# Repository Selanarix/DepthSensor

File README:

DepthSensor Project
====================

Copyright (c) 2014 Jonathan Schubert and Maximilian Hempe

About the repo
--------------
This repository contains code to realise a depth sensor by using an arduino uno and a differential pressure sensor. By transfering the pressure to water depth (1cm=1hPa) the arduino messures the water depth and gives it to a server, which produces a graph on a webpage. We do not give any garantee, but in tests it worked very well.

Purpose
--------
The Project should give a cost efficient method to messure the amount of water in an underground cistern. Additionally it can give statistics about water usage peak times.

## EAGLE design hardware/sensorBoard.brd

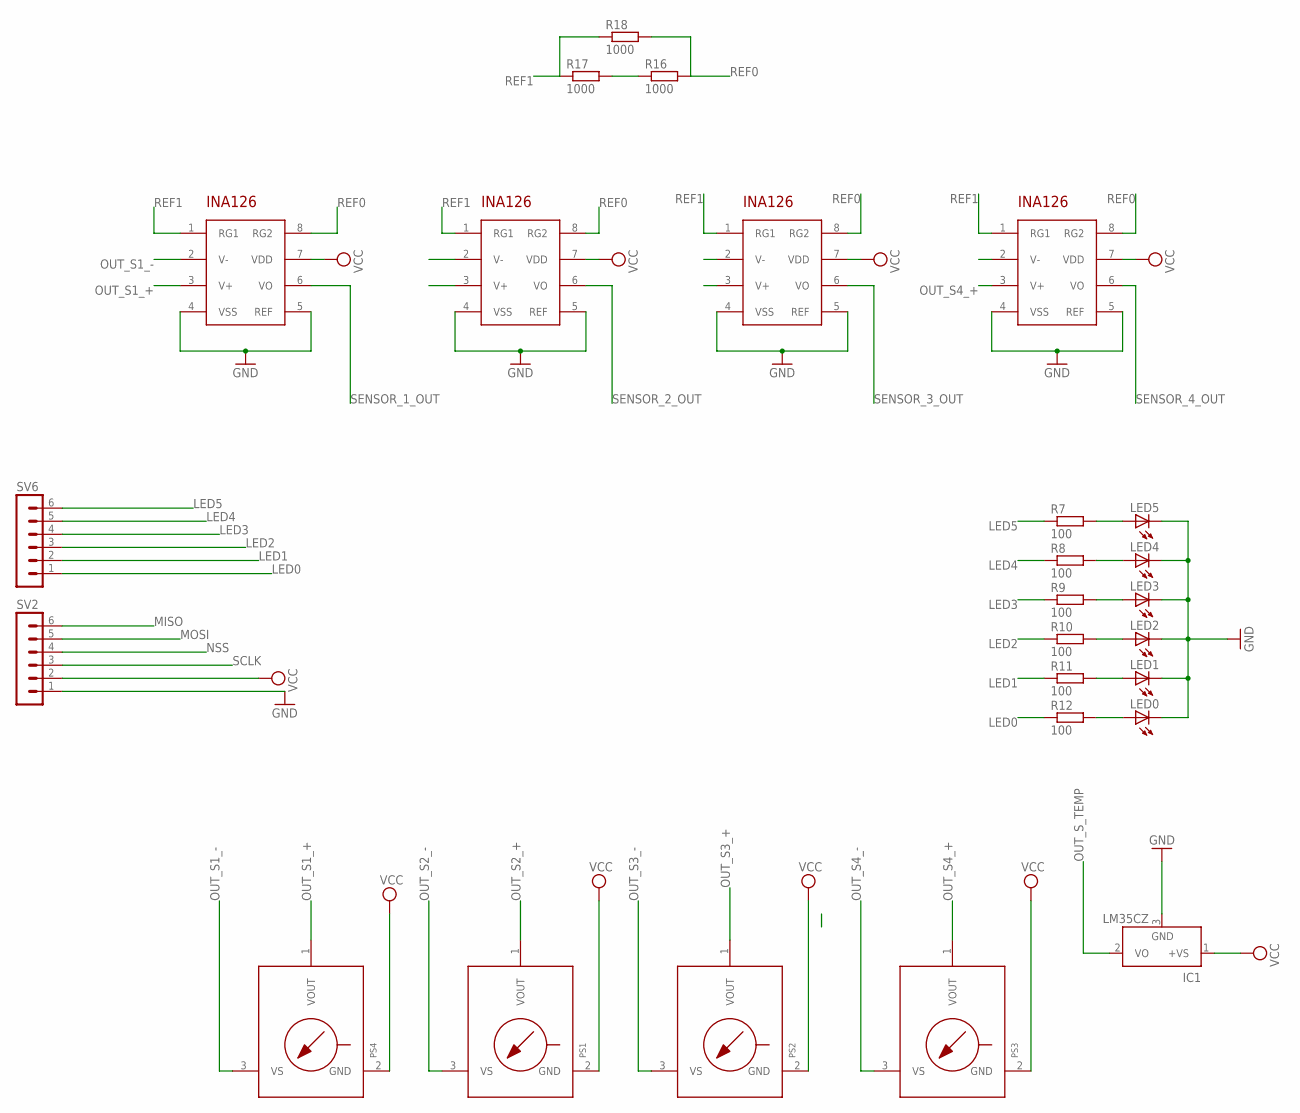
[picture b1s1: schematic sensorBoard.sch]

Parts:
IC1: LM35CZ; TO92
LED0, LED1, LED2, LED3, LED4, LED5: LED3MM
PS1, PS2, PS3, PS4: MPX-867B-H; 867B-H
R7, R8, R9, R10, R11, R12: 100; 0207/10
R16, R17, R18: 1000; 0207/10
SV2, SV6: MA06-1
U$1, U$2, U$3, U$4: INA126; SO-08

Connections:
GND: IC1.3 (GND), LED0.K (C), LED1.K (C), LED2.K (C), LED3.K (C), LED4.K (C), LED5.K (C), SV2.1, U$1.4 (VSS), U$1.5 (REF), U$2.4 (VSS), U$2.5 (REF), U$3.4 (VSS), U$3.5 (REF), U$4.4 (VSS), U$4.5 (REF)
LED0: R12.1, SV6.1
LED1: R11.1, SV6.2
LED2: R10.1, SV6.3
LED3: R9.1, SV6.4
LED4: R8.1, SV6.5
LED5: R7.1, SV6.6
MISO: SV2.6
MOSI: SV2.5
unnamed: LED5.A, R7.2
unnamed: R16.1, R17.2
unnamed: LED4.A, R8.2
unnamed: LED3.A, R9.2
unnamed: LED2.A, R10.2
unnamed: LED1.A, R11.2
unnamed: LED0.A, R12.2
NSS: SV2.4
OUT_S1_+: PS4.1 (VOUT)
OUT_S1_-: PS4.3 (VS)
OUT_S2_+: PS1.1 (VOUT)
OUT_S2_-: PS1.3 (VS)
OUT_S3_+: PS2.1 (VOUT)
OUT_S3_-: PS2.3 (VS)
OUT_S4_+: PS3.1 (VOUT)
OUT_S4_-: PS3.3 (VS)
OUT_S_TEMP: IC1.2 (VO)
REF0: R16.2, R18.2
REF1: R17.1, R18.1
SCLK: SV2.3
SENSOR_1_OUT: U$4.6 (VO)
SENSOR_2_OUT: U$1.6 (VO)
SENSOR_3_OUT: U$2.6 (VO)
SENSOR_4_OUT: U$3.6 (VO)
VCC: IC1.1 (+VS), PS1.2 (GND), PS2.2 (GND), PS3.2 (GND), PS4.2 (GND), SV2.2, U$1.7 (VDD), U$2.7 (VDD), U$3.7 (VDD), U$4.7 (VDD)

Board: 2 copper layers, 26 parts (0 on the bottom side), 17 nets, no tracks yet.

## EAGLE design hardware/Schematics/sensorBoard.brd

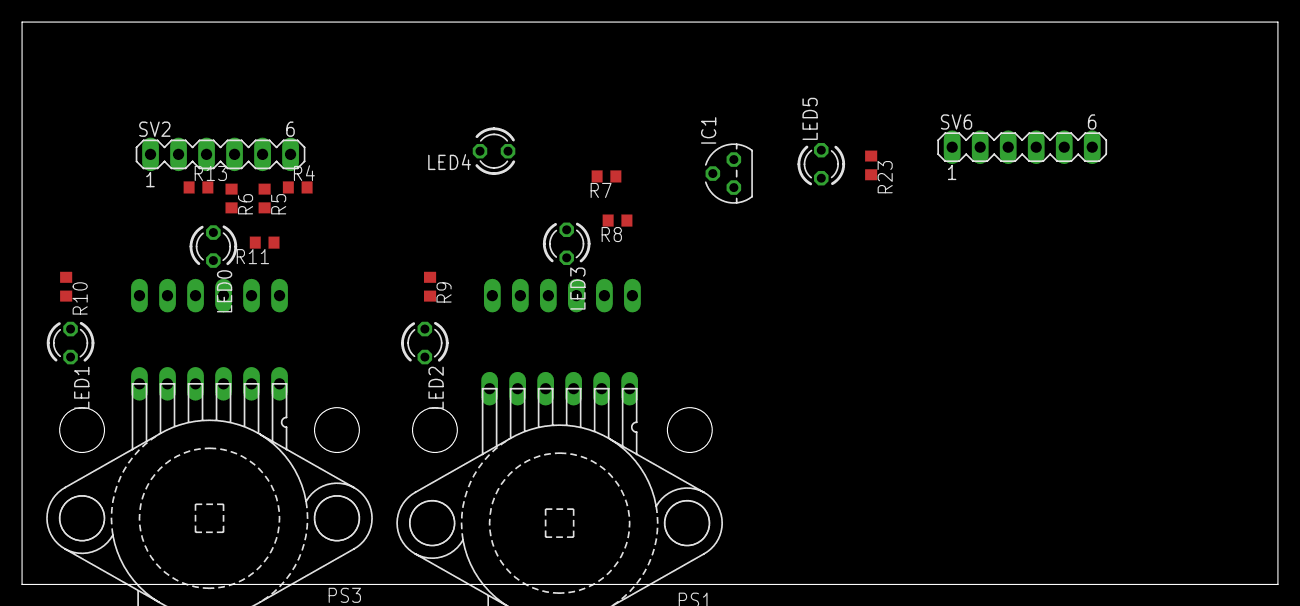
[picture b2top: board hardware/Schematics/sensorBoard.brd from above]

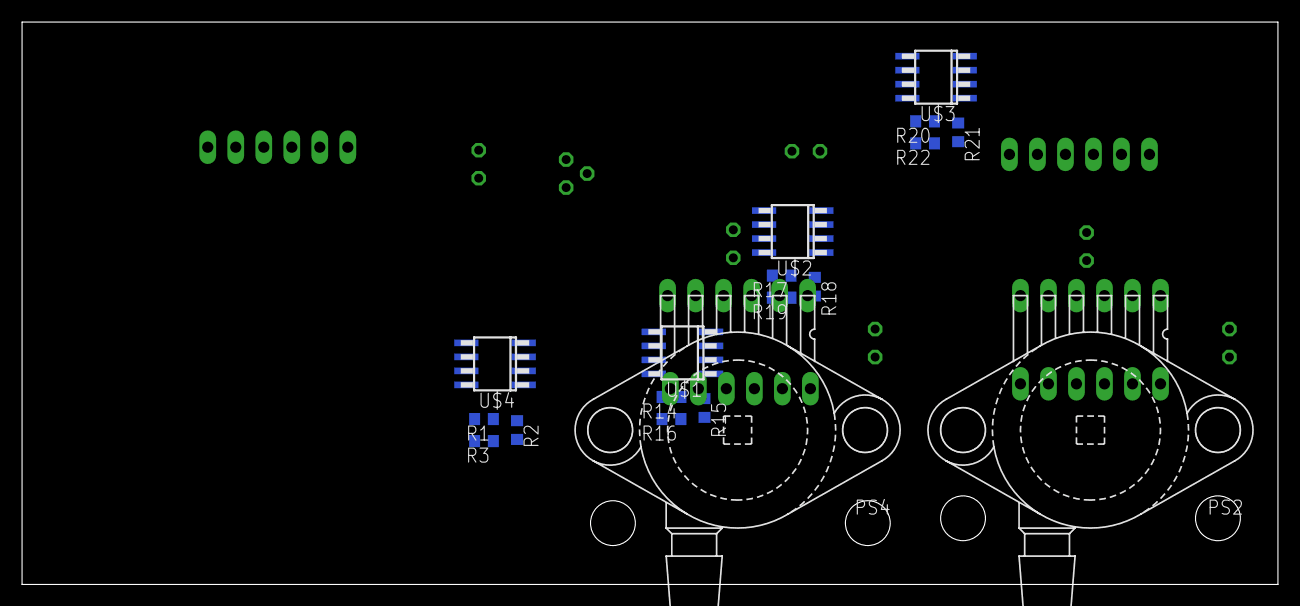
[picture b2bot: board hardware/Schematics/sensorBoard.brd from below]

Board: 2 copper layers, 113.9 x 51.0 mm, 39 parts (18 on the bottom side), 30 nets, no tracks yet.

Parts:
IC1: LM35CZ; TO92
LED0, LED1, LED2, LED3, LED4, LED5: LED3MM
PS1, PS2, PS3, PS4: 867B-H
R1, R2, R3, R14, R15, R16, R17, R18, R19, R20, R21, R22: 1000; R0603
R4, R5, R6, R13: 100k; R0603
R7, R8, R9, R10, R11, R23: 100; R0603
SV2, SV6: MA06-1
U$1, U$2, U$3, U$4: INA126; SO-08

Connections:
GND: IC1.3, LED0.K, LED1.K, LED2.K, LED3.K, LED4.K, LED5.K, SV2.1, U$1.4, U$1.5, U$2.4, U$2.5, U$3.4, U$3.5, U$4.4, U$4.5
LED0: R11.1, SV6.1
LED1: R10.1, SV6.2
LED2: R9.1, SV6.3
LED3: R8.1, SV6.4
LED4: R7.1, SV6.5
LED5: R23.1, SV6.6
MISO: R4.1, R4.2, SV2.6
MOSI: R5.1, R5.2, SV2.5
unnamed: R2.2, R3.2, U$4.8
unnamed: R1.1, R3.1, U$4.1
unnamed: LED5.A, R23.2
unnamed: R15.2, R16.2, U$1.8
unnamed: R1.2, R2.1
unnamed: R14.1, R16.1
unnamed: R14.2, R15.1
unnamed: LED4.A, R7.2
unnamed: R17.1, R19.1, U$2.1
unnamed: LED3.A, R8.2
unnamed: LED2.A, R9.2
unnamed: LED1.A, R10.2
unnamed: LED0.A, R11.2
unnamed: R18.2, R19.2, U$2.8
unnamed: R20.1, R22.1, U$3.1
unnamed: R21.2, R22.2, U$3.8
unnamed: R17.2, R18.1
unnamed: R20.2, R21.1
NSS: R6.1, R6.2, SV2.4
SCLK: R13.1, R13.2, SV2.3
VCC: IC1.1, PS1.2, PS2.2, PS3.2, PS4.2, SV2.2, U$1.7, U$2.7, U$3.7, U$4.7

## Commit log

2014-01-09 init commit
2014-01-09 add callback functions for errors
2014-01-09 fix sign problem, modify measurment function remove retries if avg value is not in range
2014-01-09 add datasheet of sensor
2014-01-10 check in of "arduino project" -depthSensor.ino file must be in depthSensor directory! -Header must be somewhere in the depthSensor directory
2014-01-10 init commit for web frontend
2014-01-10 Analog Input transformed to kPa (does not work propper)
2014-01-10 fix syntax bugs, and get it running in first simple version
2014-01-10 init commit of data evaluation frontend page
2014-01-10 add graph drawing framework
2014-01-10 start to rewrite input.php using xml files to store data, fix syntax bugs of index.php
2014-01-11 complete xml handling. And test. Problem: list of measurements is still unformated. Don't know why...
2014-01-12 -Corrected pressure formula -output in V, hPa and cm (hPa=cm)
2014-01-12 add datasheet of new sensor
2014-01-12 include Readme file
2014-01-12 index.php parses xml now. Also fix some spelling errors in code and xml
2014-01-12 index.php add simple html page with debug output
2014-01-12 -Code for LAN Board (not finished)
2014-01-12 add document structure comments and export c to own file
2014-01-12 included graph generation to index.php (could not test because gdlib is not working)
2014-01-12 fix bugs of index.php. Added img to html part of file. Still lots of warnings.
2014-01-12 program to generate 3d tank liquit level graphic
2014-01-12 add depthSensor.c to repo. Removed unused code
2014-01-12 changed statics title still errors on index.php
2014-01-13 cleared php errors in index.php missing: label of x-axis
2014-01-13 change document structure. Fix bug with wrong function name measureDepth
2014-01-13 -Arduino Network konfig is working -PUT on Arduino works with server IP -Statistics on WebFrontend are working
2014-01-13 Add logging for input.php to write errors to external log file
2014-01-13 WebFrontend: Index with filled Graph
2014-01-13 add example for jquery image autoreload in development file tankImgCreate
2014-01-13 -input without client-feedback -enhanced index.php
2014-01-13 index with selfloading graph changed http connect function
2014-01-13 changed project structure of web folder. Added javascript for autoreload of image. Remove unused example code
2014-01-13 generate log and sensorData folder
2014-01-13 fix bugs of javascript and index.php. Should work now if dynPicProcessing of graph is working as well
2014-01-13 change percentage calculation of the dynamic tank image. Fixed mapping in central data structure between sensor ID and sensor data was random before... My fault sry
2014-01-13 -design for webFrontend with bootstrap
2014-01-13 -corrected path-errors in webFrontend.
2014-01-13 -include of header and footer in Frontend -statistics for multiple SensorData
2014-01-14 working version of Frontend and DepthMessurement
2014-01-14 add tank image reload to javascript. Still needs some code review. Add tags to index.php to test reload of image
2014-01-15 change testseries value to double to be able to get bether average results
2014-01-15 Added data sheet for amplifier and move data sheets to own folder
2014-01-15 added first aproach of an sensor board. Not ready yet. Just first aproach. ADC is missing and Opamp isn't connected yet
2014-01-15 added two new fields to xml for sensor type and its unit.
2014-01-15 -basic function for temp sensor -corrected regular update in webFrontend
2014-01-15 restructured project. Add several files for each of the componentes of the project
2014-01-16 print debug info to serial
2014-01-16 wired amplifier and start to set up SPI for ADC in schematic
2014-01-16 add first aproach of HAL for arduino platform. This allows simple transformation for other platforms.
2014-01-16 Statistics without fixed Y-Axis Statistics: Y-Axis gets description from xml file
2014-01-16 corrected little misstakes
2014-01-16 pictures to illustrate a scenario
2014-01-16 add images of oszi showing problem with sensor MPX2100
2014-01-16 virtual tanks in each page's header
2014-01-16 -basic function for new pressure sensor MPX2100DP
2014-01-16 remove color of graph out of project
2014-01-16 change display for different sensor types. Changed name from depthMeasurements to measurements to stay more generally
2014-01-17 build sensor sandwich board to get it smaller. Still waiting for the ADC we would like to use
2014-01-17 added volume information to tank image. Avoid img tag placement for tank image in case of temperatur sensor
2014-01-17 add serial logger file to project. Not used by all the other files atm. Still work to do :-)
2014-01-17 changed name of datasheet ina126
2014-01-18 -basic function for external adc (8bit) with spi and cs on pin9 (only working without ethernet shield)
2014-01-18 added datasheet for ATmega328
2014-01-18 Schematics of Ethernet Shield and Arduino r3 (we use r2 but it is quite similar)
2014-01-18 integrated logger to rest of project. Completed first version of hal for arduino
2014-01-20 own folder for sensorBoard PCB
2014-01-20 -basic function for 12bit ADC connected over SPI -Roadmap for further ideas to implement
2014-01-20 add first software design diagram for arduino. Start writing driver vor ADC
2014-01-21 Changes in WebFrontend: -no more carousel classes in Header -watertanks in Header are aligned -seperated statistics per SensorType -auto links in Dropdown at Statistics Menu in NavigationBar -auto-fo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
2014-01-21 export testSeries methods to stay general for different sensors. Add driver for ADC. All componentsuntested atm.
2014-01-21 added missing '='
2014-01-23 Datasheet for npn transistor
2014-01-23 changes for propper working ADC (made in Lab)
2014-01-24 start to set up for new depth sensor test
2014-01-24 1.fixed bugs in ADC driver for ADC test by introducing warm up delay. 2. Tested and integrated testSeries abstraction to depth and temperature sensor 3. write temperatur sensor based on this abstract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
2014-01-24 Datasheet for diods included in the Starter Kit
2014-01-27 set up hal basic function without using arduino framework. Set up HAL for external ADC reading. Start to use only function from my HAL instead of arduino framework.
2014-01-27 add parameter for depth sensor to differ between sensor types. Read function of sensor is now sensor dependent.
2014-01-27 Analog Amplifier with Simulation and Messurements
2014-01-31 add critical section while spi communication
2014-01-31 start writing driver for temperatur sensor
2014-01-31 forgot to add this last time. sry
2014-01-31 change sensor functions to use oop methods. Sensor under simulation mode atm.
2014-02-01 start writing driver for TMP102 temperature sensor board using I2C
2014-02-02 completed driver for tmp102. Still untested
2014-02-02 try to use new sensor functionality out of main. Is not working atm
2014-02-03 Move log messages to flash by using F(). Rewrite testSeries and temperatur Sensor. Untested atm
2014-02-03 Messergebnisse der Verstärkerschaltung (Temp Sensor)
2014-02-03 Moved strings of log messages to flash by using F(). Rewrote depth sensor to fit the into the new structure. Fixed all compiler errors. Next step is testing on platform
2014-02-03 datasheet for new dethSensor mpx5100
2014-02-04 add support for hil to the sensors. At them moment they are not using HAL because of test data out of static variable
2014-02-04 function for new MPX5100GP Sensor
2014-02-04 Change structure to allow measure method to access object's data. Add temp sensor support for TMP102.
2014-02-04 import of readSensor-Function for Pressure Sensor mpx5100 changes to make solution compilable
2014-02-04 change depth sensor to fit new function pointer for measure functions
2014-02-04 add volatile to hardware registers
2014-02-07 add small bug with false error log for average measurement
2014-02-09 add missing header... Sorry max
2014-02-09 formula for mxp5100 (adc->cm)
2014-02-10 init checkin for display driver. Add method to read directly millivolt from the HAL
2014-02-10 test and fix bugs in temperature sensor driver
2014-02-10 add realtime clock for hw sleep of processor
2014-02-12 add log level to controll output data
2014-02-12 add debug level for measurement result in test series. Formular of temperature from sensor is not correct
2014-02-12 Formula for lm35 with ampifier
2014-02-12 add digital temperatur sensor to sensorBoard to compare analog value
2014-02-14 add functions for display driver. New global seperator line in logger
2014-02-17 start writing display controller for project
2014-02-17 add function to display flash string on display
2014-02-17 New formula for calculating amplified temp sensor
2014-02-17 updated tempSensor formula for further testing
2014-02-17 add tick function to realtime clock
2014-02-17 -Test with new Temp Formula and different tubes -rounding of depth average
2014-02-18 add name of sensor to debug output. Test successfull init system check for main loop
2014-03-04 fix bug with flash string in display driver. Problem with the deleting writing on display still unsolved
2014-03-05 fix bug in display driver with or and xor. moved strings to flash in general types file. Still problem with clearing chars after writing
2014-03-14 fix bug with overwriting chars in display driver. Add main to display measurement on display
2014-03-14 add macro to enable disable display functionality. Error management on display is still not finish
2015-01-27 modify project
2015-01-27 local folder
2015-01-27 Project Cleanup
2015-01-30 Add missing source file. Try to solve problem with file rights.
2015-01-30 working dir change
